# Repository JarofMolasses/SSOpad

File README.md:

### Firmware
Uses QMK firmware, see: https://github.com/JarofMolasses/qmk_firmware/tree/master/keyboards/ssopads

### Photos
V1.2 Teensy, with underglow LEDs

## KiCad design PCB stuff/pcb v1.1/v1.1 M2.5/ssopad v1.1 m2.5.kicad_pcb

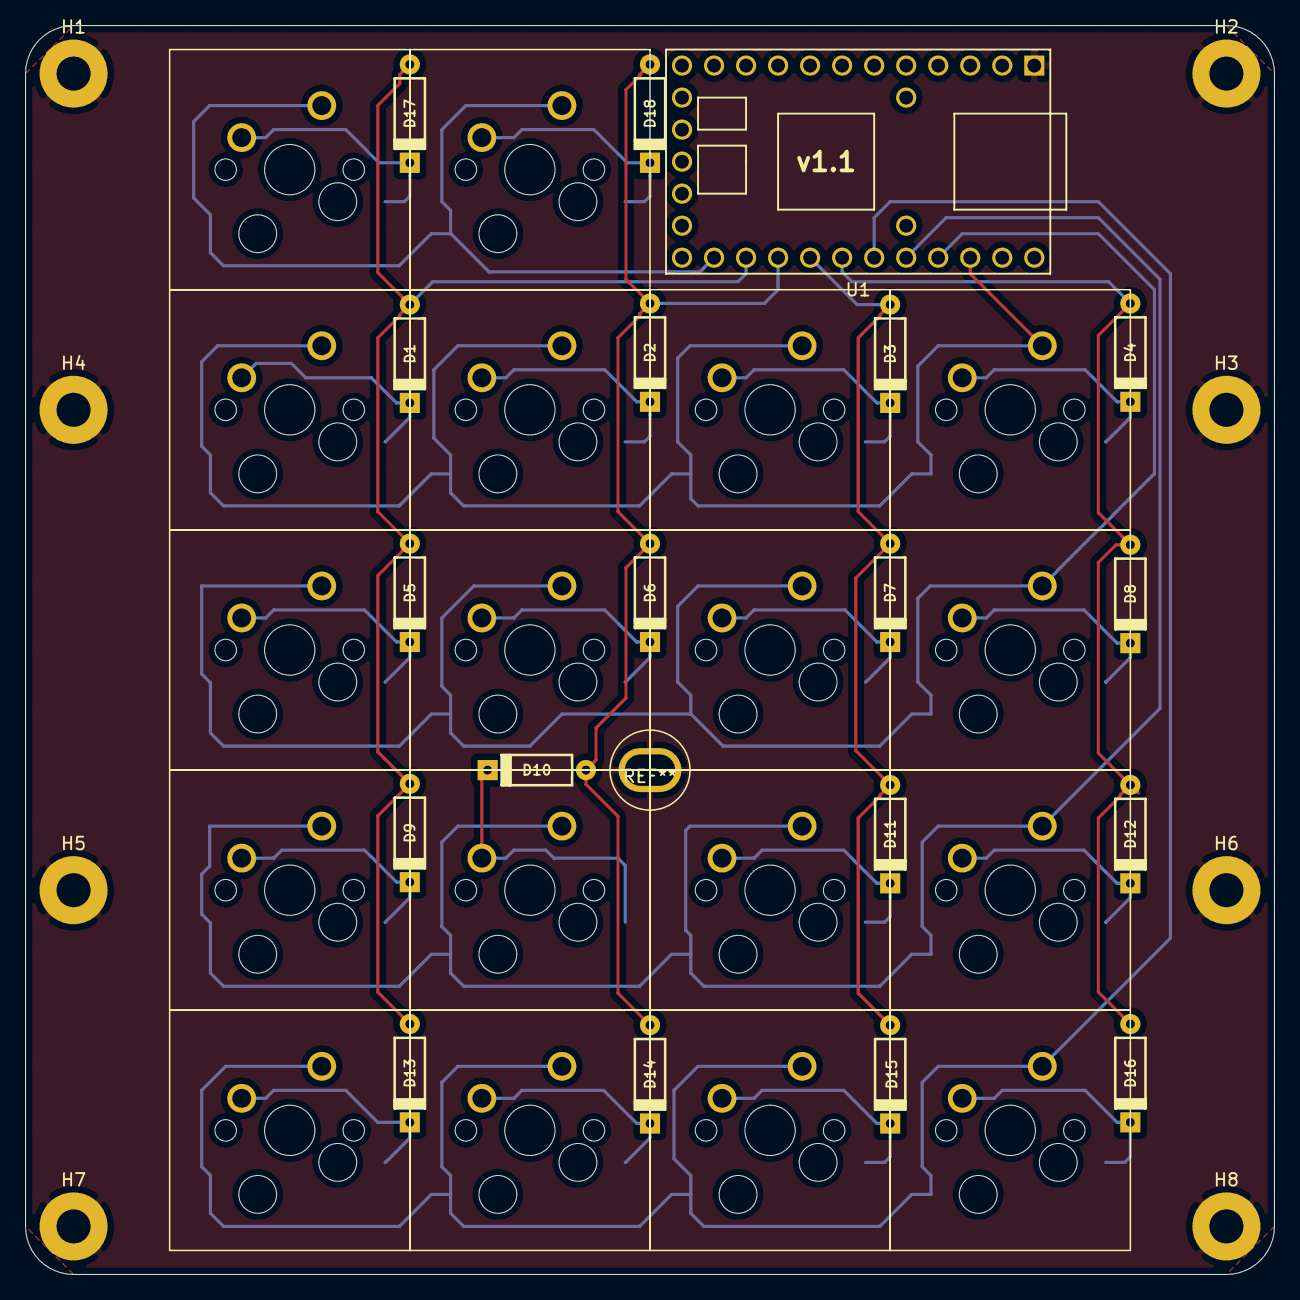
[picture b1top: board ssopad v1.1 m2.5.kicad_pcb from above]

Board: 2 copper layers, 99.1 x 99.1 mm, 45 parts (0 on the bottom side), 28 nets.

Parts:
D1, D2, D3, D4, D5, D6, D7, D8, D9, D10, D11, D12, D13, D14, D15, D16, D17, D18: DIODE; D_axial
H1, H2, H3, H4, H5, H6, H7, H8: MountingHole_Pad; MountingHole_2.7mm_Pad
SW1: 7; Kailh_socket_optional100
SW2: 8; Kailh_socket_optional100
SW3: 9; Kailh_socket_optional100
SW4: -; Kailh_socket_optional100
SW5: 4; Kailh_socket_optional100
SW6: 5; Kailh_socket_optional100
SW7: 6; Kailh_socket_optional100
SW8: *; Kailh_socket_optional100
SW9: 1; Kailh_socket_optional100
SW10: 2; Kailh_socket_optional100
SW11: 3; Kailh_socket_optional100
SW12: +; Kailh_socket_optional100
SW13: 0; Kailh_socket_optional100
SW14: .; Kailh_socket_optional100
SW15: /; Kailh_socket_optional100
SW16: Enter; Kailh_socket_optional100
SW17: Blank1; Kailh_socket_optional100
SW18: Blank2; Kailh_socket_optional100
U1: Teensy2.0

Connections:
COL0: D1.2, D5.2, D9.2, D13.2, D17.2, U1.20
COL1: D2.2, D6.2, D10.2, D14.2, D18.2, U1.21
COL2: D3.2, D7.2, D11.2, D15.2, U1.22
COL3: D4.2, D8.2, D12.2, D16.2, U1.23
GND: H1.1, H2.1, H3.1, H4.1, H5.1, H6.1, H7.1, H8.1, U1.1
unnamed: D1.1, SW1.2
unnamed: D2.1, SW2.2
unnamed: D3.1, SW3.2
unnamed: D4.1, SW4.2
unnamed: D5.1, SW5.2
unnamed: D6.1, SW6.2
unnamed: D7.1, SW7.2
unnamed: D8.1, SW8.2
unnamed: D9.1, SW9.2
unnamed: D10.1, SW10.2
unnamed: D11.1, SW11.2
unnamed: D12.1, SW12.2
unnamed: D13.1, SW13.2
unnamed: D14.1, SW14.2
unnamed: D15.1, SW15.2
unnamed: D16.1, SW16.2
unnamed: D17.1, SW17.2
unnamed: D18.1, SW18.2
ROW0: SW13.1, SW14.1, SW15.1, SW16.1, U1.24
ROW1: SW9.1, SW10.1, SW11.1, SW12.1, U1.25
ROW2: SW5.1, SW6.1, SW7.1, SW8.1, U1.26
ROW3: SW1.1, SW2.1, SW3.1, SW4.1, U1.27
ROW4: SW17.1, SW18.1, U1.19
